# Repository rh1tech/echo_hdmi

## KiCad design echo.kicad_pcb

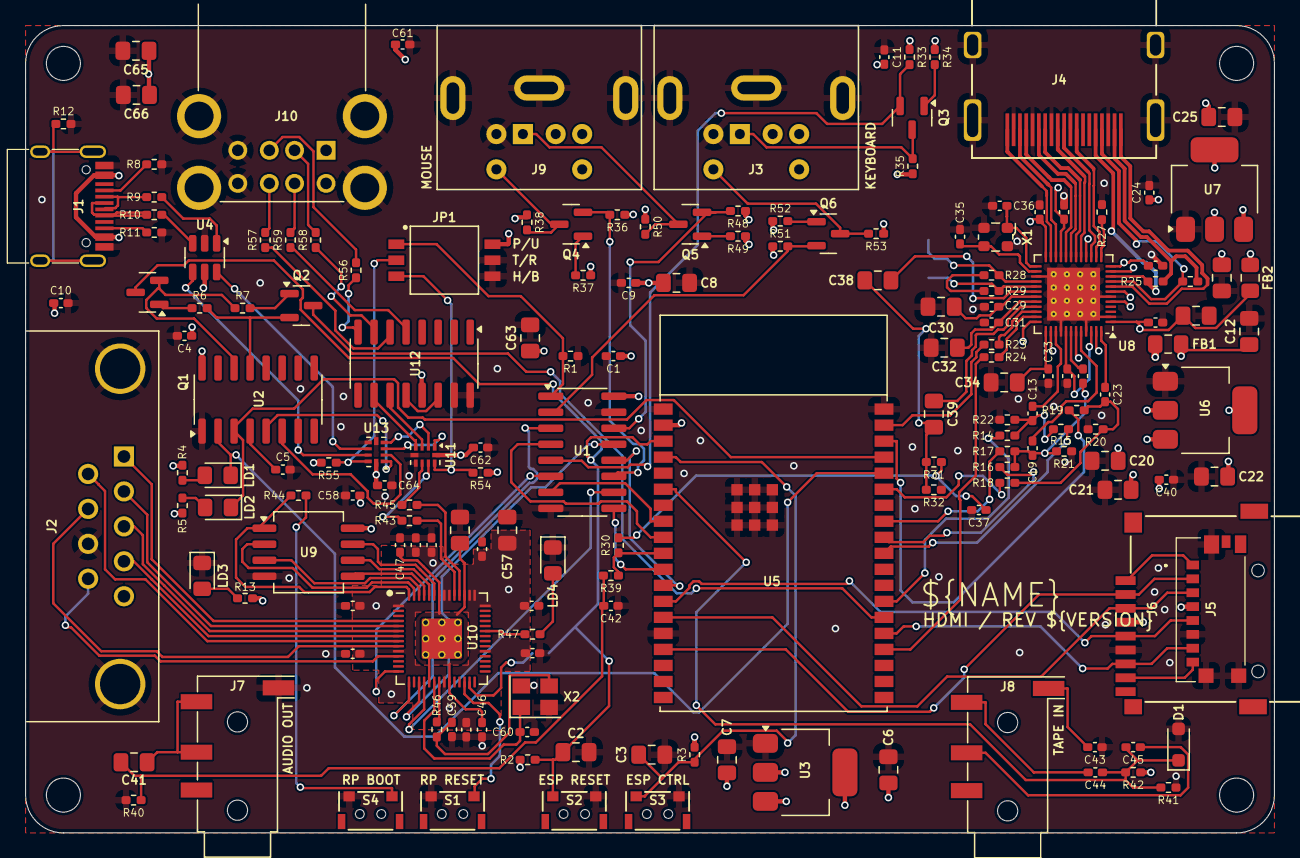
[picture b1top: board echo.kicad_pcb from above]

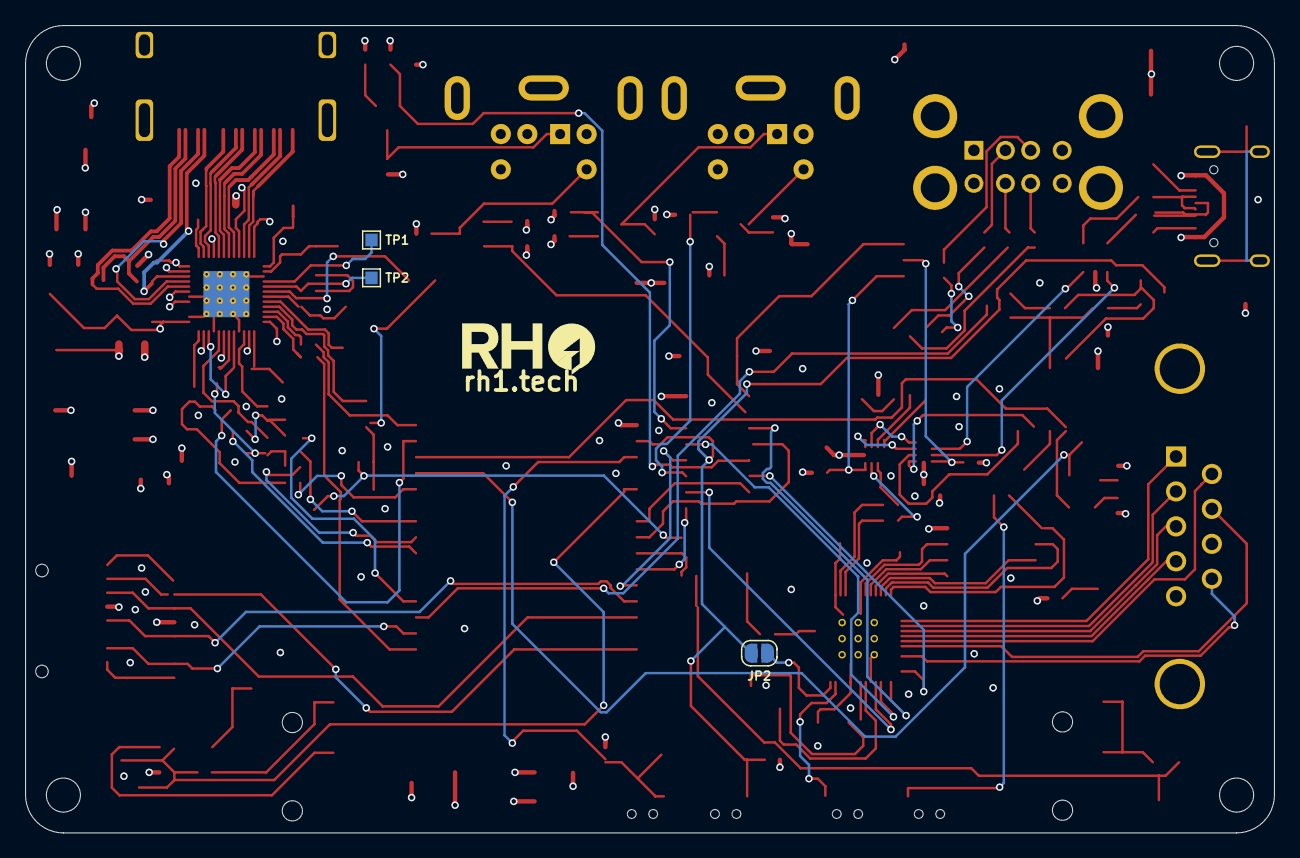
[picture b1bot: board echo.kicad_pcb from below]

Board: 4 copper layers, 99.0 x 64.0 mm, 175 parts (3 on the bottom side), 148 nets.

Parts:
C1, C4, C5, C9, C10, C11, C13, C14, C15, C16, C17, C18, C19, C23, C24, C37, C40, C43, C44, C45, C46, C47, C48, C49, C50, C51, C52, C53, C54, C55, C58, C61, C62, C64: 100n; Capacitor (0402)
C2, C3, C22, C26, C38, C39, C56, C57: 1u; Capacitor (0805)
C6, C7, C8, C12, C20, C21, C25, C28, C41, C65, C66: 10u; Capacitor (0805)
C27: 1n; Capacitor (0402)
C29, C31, C33: 220n; Capacitor (0402)
C30, C32, C34, C63: 4.7u; Capacitor (0805)
C35, C36, C59, C60: 15p; Capacitor (0402)
C42: 33n; Capacitor (0402)
D1: Zener 3V3; Diode (SOD-323)
FB1, FB2: 220R; Inductor (0805)
H1, H2, H3, H4: MountingHole; Mounting Hole (2.7mm)
J1: USB4215-03-A; USB Type C
J2: D-SUB 9 Male; D-SUB (9 pin, male, top mount)
J3, J9: MDC-036; MiniDIN (6 Pin, female)
J4: DC3RX19JA2; HDMI (female)
J5: 0475710001; MicroSD (SMD, short)
J6: 104031-0811; MicroSD (SMD, long)
J7, J8: PJ-320D; Jack (3.5mm, PJ-320D)
J10: SS-52100-004; USB Type A (stacked)
JP1: Main Jumpers; SW_DS05-127-2-03BK-SMT-TR
JP2: ESP-RP RST; Jumper (solder)
LD1: Orange (TX); LED (0805)
LD2: Orange (RX); LED (0805)
LD3: Green (Power); LED (0805)
LD4: Blue (GPIO25); LED (0805)
Q1, Q2: BSS138; SOT-23
Q3, Q4, Q5, Q6: AO3400A; SOT-23
R1, R2, R3, R41, R42, R54, R55: 10K; Resistor (0402)
R4, R5: 1.5K; Resistor (0402)
R6, R7: 2.2K; Resistor (0402)
R8, R11: 5.1K; Resistor (0402)
R9, R10, R56, R57, R58, R59: 22R; Resistor (0402)
R12: 1M; Resistor (0402)
R13, R27, R32, R44, R46, R47: 1K; Resistor (0402)
R14, R16, R18: 800R; Resistor (0402)
R15, R17, R19: 400R; Resistor (0402)
R20, R21, R22: 75R; Resistor (0402)
R23, R24, R39: 100R; Resistor (0402)
R25, R26: 2K; Resistor (0402)
R28, R29, R31, R34, R37, R49, R52: 4.7K; Resistor (0402)
R30: 330R; Resistor (0402)
R33, R35, R36, R38, R48, R50, R51, R53: 22K; Resistor (0402)
R40: 150R; Resistor (0402)
R43, R45: 27R; Resistor (0402)
S1: RP Reset; TACT-SIDE-4623
S2: ESP Reset; TACT-SIDE-4623
S3: ESP Ctrl; TACT-SIDE-4623
S4: RP Boot; TACT-SIDE-4623
TP1: MS9288_SCL; TestPoint (Pad 1.0x1.0mm)
TP2: MS9288_SDA; TestPoint (Pad 1.0x1.0mm)
U1: SN74CBT3257CDR; SOP-16
U2: CH340C; SOP-16
U3: NCP1117 3.3; SOT-223
U4: USBLC6-2SC6; SOT-23-6
U5: ESP32-WROVER-E
U6: AMS1117-3.3; SOT-223
U7: AMS1117-1.8; SOT-223
U8: MS9288A; QFN 48
U9: W25Q128JVSIQ; SOIC-8
U10: RP2040; QFN 56
U11, U13: TS3USB221RSER; UQFN-10
U12: MW7211A; SOP-16
X1: 24.576 MHz; Crystal (2520)
X2: 12 MHz; Crystal (3225)

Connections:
+3V3: C6.1, C8.1, C9.1, C40.2, C48.1, C49.1, C50.1, C51.1, C52.1, C53.1, C54.1, C55.1, C57.1, C58.1, C62.2, C64.2, J5.P4 (VDD), J6.4 (VDD), R2.2, R3.2, R13.2, R33.1, R34.1, R36.1, R37.1, R48.1, R49.1, R51.1, R52.1, R54.1, R55.1, U3.2 (VO), U5.2 (3V3), U9.8 (VCC), U10.1 (IOVDD), U10.10 (IOVDD), U10.22 (IOVDD), U10.33 (IOVDD), U10.42 (IOVDD), U10.43 (ADC_AVDD), U10.44 (VREG_IN), U10.48 (USB_VDD), U10.49 (IOVDD), U11.10 (VCC), U13.10 (VCC)
/Audio Out/A_OUT: C41.1, J7.R, J7.T
/DAT1: J5.P8 (DAT1), J6.8 (DAT1)
/DAT2: J5.P1 (DAT2), J6.1 (DAT2)
/ESP_EN: C2.1, JP2.2 (B), Q1.3 (C), R2.1, S2.2, U5.3 (EN/CHIP_PU)
/ESP_IO0: Q2.3 (C), U5.25 (GPIO0/BOOT/ADC2_CH1)
/ESP_IO1: LD2.1 (K), U2.3 (RxD), U5.35 (U0TXD/GPIO1)
/ESP_IO2: J5.P7 (DAT0), J6.7 (DAT0), U5.24 (ADC2_CH2/GPIO2)
/ESP_IO3: LD1.1 (K), U2.2 (TxD), U5.34 (U0RXD/GPIO3)
/ESP_IO4: R14.1, U5.26 (ADC2_CH0/GPIO4)
/ESP_IO5: R15.1, U5.29 (GPIO5)
/ESP_IO12: J5.P3 (CMD), J6.3 (CMD), U5.14 (MTDI/GPIO12/ADC2_CH5)
/ESP_IO13: J5.P2 (CD/DAT3), J6.2 (DAT3/CD), U5.16 (MTCK/GPIO13/ADC2_CH4)
/ESP_IO14: J5.P5 (CLK), J6.5 (CLK), U5.13 (MTMS/GPIO14/ADC2_CH6)
/ESP_IO15: R24.1, U5.23 (MTDO/GPIO15/ADC2_CH3)
/ESP_IO18: R16.1, U5.30 (GPIO18)
/ESP_IO19: R17.1, U5.31 (GPIO19)
/ESP_IO21: R18.1, U5.33 (GPIO21)
/ESP_IO22: R19.1, U5.36 (GPIO22)
/ESP_IO23: R23.1, U5.37 (GPIO23)
/ESP_IO25: R30.1, R39.1, U5.10 (DAC_1/ADC2_CH8/GPIO25)
/ESP_IO26: U1.9 (3A), U5.11 (DAC_2/ADC2_CH9/GPIO26)
/ESP_IO27: U1.12 (4A), U5.12 (ADC2_CH7/GPIO27)
/ESP_IO32: U1.7 (2A), U5.8 (32K_XP/GPIO32/ADC1_CH4)
/ESP_IO33: U1.4 (1A), U5.9 (32K_XN/GPIO33/ADC1_CH5)
/ESP_IO34: C44.1, C45.1, D1.1, R41.1, R42.1, U5.6 (GPIO34/ADC1_CH6)
/ESP_IO36: C3.1, R3.1, S3.2, U5.4 (SENSOR_VP/GPIO36/ADC1_CH0)
/GPIO2: J2.1, U10.4 (GPIO2)
/GPIO3: J2.2, U10.5 (GPIO3)
/GPIO4: J2.3, U10.6 (GPIO4)
/GPIO5: J2.4, U10.7 (GPIO5)
/GPIO6: J2.6, U10.8 (GPIO6)
/GPIO7: J2.7, U10.9 (GPIO7)
/GPIO8: J2.9, U10.11 (GPIO8)
/GPIO11: U1.6 (2B2), U10.14 (GPIO11)
/GPIO12: U1.3 (1B2), U10.15 (GPIO12)
/GPIO14: U1.13 (4B2), U10.17 (GPIO14)
/GPIO15: U1.10 (3B2), U10.18 (GPIO15)
/GPIO16: JP2.1 (A), U10.27 (GPIO16)
/HUB_D+: U11.3 (2D+), U12.11 (DPU)
/HUB_D-: U11.4 (2D-), U12.10 (DMU)
/KB_CLK: J3.5, Q6.3 (D), R53.2
/KB_CLK_3V: Q6.2 (S), R51.2, U1.2 (1B1)
/KB_DATA: J3.1, Q3.3 (D), R35.2
/KB_DATA_3V: Q3.2 (S), R33.2, U1.5 (2B1)
/MP1_D+: U11.1 (1D+), U13.3 (2D+)
/MP1_D-: U11.2 (1D-), U13.4 (2D-)
/MS_CLK: J9.5, Q4.3 (D), R38.2
/MS_CLK_3V: Q4.2 (S), R36.2, U1.11 (3B1)
/MS_DATA: J9.1, Q5.3 (D), R50.2
/MS_DATA_3V: Q5.2 (S), R48.2, U1.14 (4B1)
/PW_D+: U4.4 (I/O2), U13.8 (D+)
/PW_D-: U4.6 (I/O1), U13.7 (D-)
/RP2040/GPIO25: R47.2, U10.37 (GPIO25)
/RP2040/QSPI_SCLK: U9.6 (CLK), U10.52 (QSPI_SCLK)
/RP2040/QSPI_SD0: U9.5 (DI(IO0)), U10.53 (QSPI_SD0)
/RP2040/QSPI_SD1: U9.2 (DO(IO1)), U10.55 (QSPI_SD1)
/RP2040/QSPI_SD2: U9.3 (IO2), U10.54 (QSPI_SD2)
/RP2040/QSPI_SD3: U9.7 (IO3), U10.51 (QSPI_SD3)
/RP2040/QSPI_SS: R44.1, U9.1 (~CS), U10.56 (QSPI_SS)
/RP2040/XIN: C60.1, U10.20 (XIN), X2.1
/RP2040/XOUT: R46.1, U10.21 (XOUT)
/RP_D+: R43.1, U11.8 (D+)
/RP_D-: R45.1, U11.7 (D-)
/RUN: S1.1, U10.26 (RUN)
/SN74_S: JP1.1, R1.2, U1.1 (S)
/Tape In/G: C43.2, J8.S
/Tape In/L: C44.2, J8.T
/Tape In/R: C45.2, J8.R
/UMSW1: JP1.2, R55.2, U13.9 (S)
/UMSW2: JP1.3, R54.2, U11.9 (S)
/USB1_D1+: R56.1, U12.8 (DP3)
/USB1_D1-: R58.1, U12.7 (DM3)
/USB1_D2+: R57.1, U12.6 (DP2)
/USB1_D2-: R59.1, U12.5 (DM2)
/UTC_D+: U2.5 (D+), U13.1 (1D+)
/UTC_D-: U2.6 (D-), U13.2 (1D-)
/VGA to HDMI/5V: R28.2, R29.2
/VGA to HDMI/ALIN: C38.1, U8.30 (ALIN)
/VGA to HDMI/AMS_1V8: C16.1, C25.1, C26.1, FB2.1, U7.2 (VO), U8.7 (AVDD18), U8.16 (AVDD18), U8.21 (AVDD18)
/VGA to HDMI/AMS_1V8A: C14.1, C15.1, C28.1, FB2.2, U8.1 (AVDD18_ADC), U8.41 (AVDD18_ADC), U8.46 (AVDD18_ADC)
/VGA to HDMI/AMS_3V3: C18.1, C21.1, C22.1, FB1.2, U6.2 (VO), U8.5 (DVDD33), U8.11 (DVDD33), U8.24 (DVDD33), U8.36 (DVDD33)
/VGA to HDMI/AMS_3V3A: C12.1, C17.1, FB1.1, U8.12 (AVDD33), U8.38 (AVDD33), U8.43 (AVDD33), U8.47 (AVDD33)
/VGA to HDMI/ARIN: C39.1, U8.33 (ARIN)
/VGA to HDMI/B: C13.1, U8.39 (B/Pb)
/VGA to HDMI/DCCSCL: J4.15 (SCL), R25.1, U8.10 (DCCSCL)
/VGA to HDMI/DDCSDA: J4.16 (SDA), R26.1, U8.9 (DDCSDA)
/VGA to HDMI/G: C19.1, U8.44 (G/Y)
/VGA to HDMI/HDMI_5V: J4.18 (+5V), R25.2, R26.2
/VGA to HDMI/HPDT: J4.19 (HOT_PLUG_DET), U8.8 (HotPlugDetect)
/VGA to HDMI/R: C23.1, U8.48 (R/Pr)
/VGA to HDMI/SCL: R28.1, TP1.1, U8.28 (SCL)
/VGA to HDMI/SDA: R29.1, TP2.1, U8.29 (SDA)
/VGA to HDMI/SOG_G: C19.2, C27.2, R16.2, R17.2, R21.1
/VGA to HDMI/TMDS_CLK+: J4.10 (CLKP), U8.15 (TMDS_CLK+)
/VGA to HDMI/TMDS_CLK-: J4.12 (CLKN), U8.14 (TMDS_CLK-)
/VGA to HDMI/TMDS_D0+: J4.7 (D0P), U8.18 (TMDS-D0+)
/VGA to HDMI/TMDS_D0-: J4.9 (D0N), U8.17 (TMDS_D0-)
/VGA to HDMI/TMDS_D1+: J4.4 (D1P), U8.20 (TMDS_D1+)
/VGA to HDMI/TMDS_D1-: J4.6 (D1N), U8.19 (TMDS_D1-)
/VGA to HDMI/TMDS_D2+: J4.1 (D2P), U8.23 (TMDS_D2+)
/VGA to HDMI/TMDS_D2-: J4.3 (D2N), U8.22 (TMDS_D2-)
GND: C1.1, C2.2, C3.2, C4.2, C5.2, C6.2, C7.2, C8.2, C9.2, C10.2, C11.2, C12.2, C14.2, C15.2, C16.2, C17.2, C18.2, C20.2, C21.2, C22.2, C24.2, C25.2, C26.2, C28.2, C29.2, C30.2, C31.2, C32.2, C33.2, C34.2, C35.2, C36.2, C37.2, C40.1, C42.1, C43.1, C46.2, C47.2, C48.2, C49.2, C50.2, C51.2, C52.2, C53.2, C54.2, C55.2, C56.2, C57.2, C58.2, C59.2, C60.2, C61.2, C62.1, C63.2, C64.1, C65.2, C66.2, D1.2, J1.1 (GND), J1.12 (GND), J2.8, J3.3, J4.2 (G_D2), J4.5 (G_D1), J4.8 (G_D0), J4.11 (G_CLK), J4.17 (G_DDC/CEC), J4.20 (SHIELD1), J4.21 (SHIELD2), J4.22 (SHIELD3), J4.23 (SHIELD4), J5.G1 (GND_1), J5.G2 (GND_2), J5.G3 (GND_3), J5.P6 (VSS), J6.6 (VSS), J7.S, J9.3, J10.4 (GND1), J10.8 (GND2), J10.9 (Shield), JP1.4, JP1.5, LD3.1 (K), LD4.1 (K), R1.1, R8.1, R11.1, R12.2, R20.2, R21.2, R22.2, R27.1, R32.2, R40.1, R41.2, S1.2, S2.1, S3.1, S4.2, U1.8 (GND), U1.15 (~OE), U2.1 (GND), U3.1 (GND), U4.2 (GND), U5.1 (GND), U5.15 (GND), U5.38 (GND), U5.39 (GND_THERMAL), U6.1 (GND), U7.1 (GND), U8.2 (GND), U8.6 (GND), U8.27 (GND), U8.40 (GND), U8.45 (GND), U8.49 (EP), U9.4 (GND), U10.19 (TESTEN), U10.57 (GND), U11.5 (GND), U11.6 (~OE), U12.15 (GND), U12.16 (GND), U13.5 (GND), U13.6 (~OE), X1.2 (GND), X1.4 (GND), X2.2, X2.4
unnamed: C13.2, R14.2, R15.2, R22.1
unnamed: C23.2, R18.2, R19.2, R20.1
unnamed: C37.1, R30.2, R31.1
unnamed: C38.2, C39.2, R31.2, R32.1
unnamed: C41.2, C42.2, R39.2, R40.2
unnamed: C59.1, R46.2, X2.3
unnamed: J1.4 (CC1), R8.2
unnamed: J1.10 (CC2), R11.2
unnamed: J1.5 (DN2), J1.7 (DN1), R9.2
unnamed: J1.6 (DP1), J1.8 (DP2), R10.2
unnamed: J1.13 (SHIELD), R12.1
unnamed: J10.3 (D1+), R56.2
unnamed: J10.2 (D1-), R58.2
unnamed: J10.7 (D2+), R57.2
unnamed: J10.6 (D2-), R59.2
unnamed: LD1.2 (A), R4.1
unnamed: LD2.2 (A), R5.2
unnamed: LD3.2 (A), R13.1
unnamed: LD4.2 (A), R47.1
unnamed: Q1.1 (B), R6.1
unnamed: Q1.2 (E), R7.2, U2.14 (RTS)
unnamed: Q2.1 (B), R7.1
unnamed: Q2.2 (E), R6.2, U2.13 (DTR)
unnamed: Q3.1 (G), R34.2
unnamed: Q4.1 (G), R37.2
unnamed: Q5.1 (G), R49.2
unnamed: Q6.1 (G), R52.2
unnamed: R9.1, U4.1 (I/O1)
unnamed: R10.1, U4.3 (I/O2)
unnamed: R44.2, S4.1
unnamed: C5.1, U2.4 (3V)
unnamed: R23.2, U8.34 (HSIN)
unnamed: C33.1, C34.1, U8.37 (REFP)
unnamed: C29.1, C30.1, U8.31 (REFQ0)
unnamed: C31.1, C32.1, U8.32 (REFQ1)
unnamed: C27.1, U8.42 (SOG/Y)
unnamed: R27.2, U8.13 (SWREF1k)
unnamed: R24.2, U8.35 (VSIN)
unnamed: C36.1, U8.25 (XTI), X1.1 (OSC)
unnamed: C35.1, U8.26 (XTO), X1.3 (OSC)
unnamed: R45.2, U10.46 (USB_DM)
unnamed: R43.2, U10.47 (USB_DP)
unnamed: C46.1, C47.1, C56.1, U10.23 (DVDD), U10.45 (VREG_VOUT), U10.50 (DVDD)
unnamed: U12.12 (VD33), U12.14 (VD3)
VBUS: C1.2, C4.1, C7.1, C10.1, C11.1, C20.1, C24.1, C61.1, C63.1, C65.1, C66.1, J1.2 (VBUS), J1.11 (VBUS), J2.5, J3.4, J9.4, J10.1 (VBUS1), J10.5 (VBUS2), JP1.6, R4.2, R5.1, R35.1, R38.1, R42.2, R50.1, R53.1, U1.16 (VCC), U2.16 (VCC), U3.3 (VI), U4.5 (VBUS), U6.3 (VI), U7.3 (VI), U12.13 (VDD5)

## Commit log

2025-07-04 HW Rev 1.00
